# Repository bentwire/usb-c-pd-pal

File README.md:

# usb-c-pd-pal
100W USB C PD Power path with on board switches and current sensing.  Can take input from USB-C, Barell, or wire terminal, and output to wire terminal or USB-C.

This design can do up to 100W PD.  The switches and connectors are all rated for 5A, the max voltage is 21V so it can't do the extended power ranges.

There is a separate power path for both the 5V only and High Power paths.  The board is wired to be capable of both sink and source modes.

If you wish to make this board act as a source you will need to provide 5V to the 5V power path at the very least.

TODO:
Code forthcoming.
Still need to finish the layout.
Some parts won't be generally available until next year...

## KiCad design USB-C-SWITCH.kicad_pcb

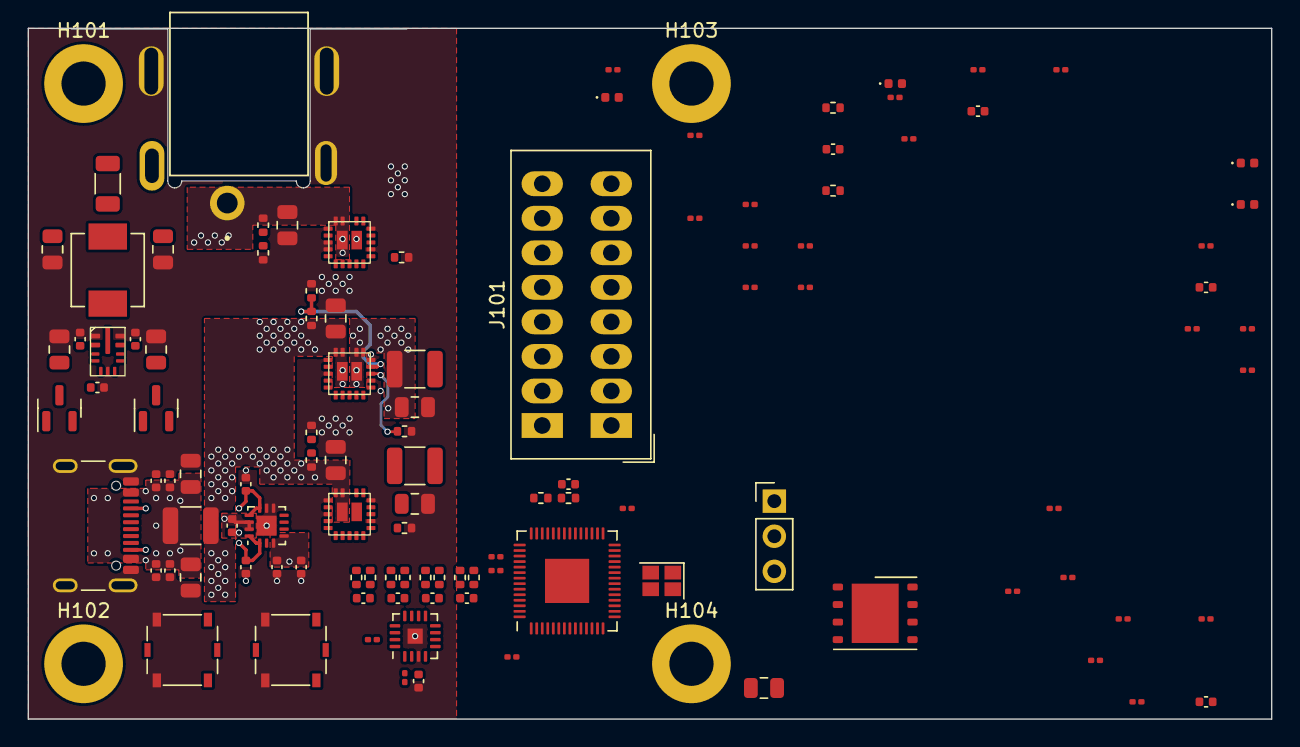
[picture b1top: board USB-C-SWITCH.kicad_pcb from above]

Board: 4 copper layers, 90.0 x 50.0 mm, 114 parts (0 on the bottom side), 70 nets.

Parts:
C201, C204, C301: 22UF 35V X5R; C_0805_2012Metric
C202, C205, C302: 10uF 35V; C_0805_2012Metric
C203, C206, C303, C404, C414: 100nF; C_0402_1005Metric
C401, C402, C406, C407, C408, C409, C419, C420: 0.1uF 50V X5R; C_0402_1005Metric
C403, C421: 1uF 10V X7S; C_0402_1005Metric
C405, C415: 0.1uF 10V X7R; C_0402_1005Metric
C410, C411, C417, C418: 4.7uF 50V X5R; C_0805_2012Metric
C412, C413: 330pF 50V; C_0402_1005Metric
C416: 11pF 50V; C_0402_1005Metric
C422, C423: 22uF 10V X5R; C_0805_2012Metric
C501, C502: 1uF 6.3V; C_0402_1005Metric
C503, C504, C505, C506, C507, C508, C509, C510, C511: 100nF 6.3V; C_0201_0603Metric
C512, C513: 27pF; C_0201_0603Metric
D401, D402: PMEG3005CT; SOT-23
D501, D502, D503, D504: TZ-P2-0402GTIA1-0.45T; LED_0402_1005Metric
H101, H102, H103, H104: MountingHole; MountingHole_3.2mm_M3_ISO7380_Pad
J101: Conn_01x08_Socket; TerminalBlock_Phoenix_PTSM-0,5-8-2.5-H-THR_1x08_P2.50mm_Hor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
J201: PJ-068B-SMT-TR; CUI_PJ-068B-SMT-TR
J401: USB_C_Receptacle_USB2.0; USB_C_Receptacle_GCT_USB4105-xx-A_16P_TopMnt_Horizontal
J501: Conn_01x03; PinHeader_1x03_P2.54mm_Vertical
L401: 6.8uH IHLP2020BZER6R8M01; L_Vishay_IHLP-2020
R201, R301, R401: 0.018R 1W 1%; R_1210_3225Metric
R202, R208: 165K 1%; R_0402_1005Metric
R203, R204, R303, R304, R402, R403, R406, R407: 10R; R_0402_1005Metric
R205, R210, R305: 10K 1%; R_0402_1005Metric
R206, R212, R307: 470R; R_0402_1005Metric
R207, R209, R306, R404, R405, R503, R504, R507: 10K; R_0201_0603Metric
R211: 5.62K 1%; R_0402_1005Metric
R213: 1K 1%; R_0402_1005Metric
R302: 34K 1%; R_0402_1005Metric
R408: 0.060R 1W 1%; R_1206_3216Metric
R409: 100K; R_0402_1005Metric
R410: 43.2K; R_0402_1005Metric
R501, R502: 4.7K; R_0201_0603Metric
R505, R506: 27R4; R_0201_0603Metric
R508, R509: 1K; R_0201_0603Metric
R510, R511, R512, R513: 470R; R_0201_0603Metric
SW501: RUN; SW_SPST_Panasonic_EVQPL_3PL_5PL_PT_A15
SW502: BOOT; SW_SPST_Panasonic_EVQPL_3PL_5PL_PT_A15
U201, U202, U301: UCS3205; 19-VQFN-Q8A-3x3x0.9-2EP
U401: FUSB302BMPX; WQFN-14-1EP_2.5x2.5mm_P0.5mm_EP1.45x1.45mm
U402: PAC1954x-x4MX; VQFN-16-1EP_3x3mm_P0.5mm_EP1.1x1.1mm
U403: LMR36006CRNX; TI-RNX0012A-VQFN-HR
U501: W25Q128JVPIQ; WSON-8-1EP_6x5mm_P1.27mm_EP3.4x4.3mm
U502: RP2040; QFN-56-1EP_7x7mm_P0.4mm_EP3.2x3.2mm
Y501: 12.000 MHz; Crystal_SMD_EuroQuartz_X22-4Pin_2.5x2.0mm

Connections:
+3.3VP: C401.1, C402.1, C403.1, C405.2, C501.2, C503.2, C504.2, C505.2, C506.2, C507.2, C508.2, C511.1, R207.1, R209.1, R306.1, R404.1, R405.1, R407.1, R408.2, R501.1, R502.1, R503.1, R504.1, R507.1, U401.3 (VDD), U401.4 (VDD), U401.12 (VCONN), U401.13 (VCONN), U402.2 (V_{DD}), U501.8 (VCC), U502.1 (IOVDD), U502.10 (IOVDD), U502.22 (IOVDD), U502.33 (IOVDD), U502.42 (IOVDD), U502.43 (ADC_AVDD), U502.44 (VREG_IN), U502.48 (USB_VDD), U502.49 (IOVDD)
/5V Power Path/5V-PP-VS+: C303.1, R303.2, U402.8 (SENSE3+)
/5V Power Path/5V-PP-VS-: C303.2, R304.2, U402.7 (SENSE3-)
/5V Power Path/VUSB_5V_DIR: U301.4 (DIR), U502.35 (GPIO23)
/5V Power Path/VUSB_5V_DSC: U301.5 (DSC), U502.36 (GPIO24)
/5V Power Path/VUSB_5V_EN: U301.2 (EN), U502.34 (GPIO22)
/5V Power Path/VUSB_5V_SENSE: C302.1, R301.1, R303.1, U301.16 (VOUT), U301.17 (VOUT), U301.VOUT
/5V Power Path/VUSB_5V_~FAULT: R306.2, U301.11 (~FAULT), U502.37 (GPIO25)
/PD Current Sense and USB-C/D+: J401.A6 (D+), J401.B6 (D+), R505.1
/PD Current Sense and USB-C/D-: J401.A7 (D-), J401.B7 (D-), R506.1
/PD Current Sense and USB-C/PD-SENSE-~ALERT1: R404.2, U402.1 (SLOW), U502.5 (GPIO3)
/PD Current Sense and USB-C/PD-SENSE-~ALERT2: R405.2, U402.15 (GPIO), U502.6 (GPIO4)
/PD Current Sense and USB-C/PD-SENSE-~PWRDN: U402.16 (~PWRDN), U502.7 (GPIO5)
/PD Current Sense and USB-C/PP-VS+: C203.1, R203.2, U402.13 (SENSE2+)
/PD Current Sense and USB-C/PP-VS-: C203.2, R204.2, U402.14 (SENSE2-)
/PD Current Sense and USB-C/SCL: R502.2, U401.6 (SCL), U402.4 (SCL), U502.3 (GPIO1)
/PD Current Sense and USB-C/SDA: R501.2, U401.7 (SDA), U402.5 (SDA), U502.2 (GPIO0)
/PD Current Sense and USB-C/USB-C-~INT: R503.2, U401.5 (INT_N), U502.4 (GPIO2)
/PD Current Sense and USB-C/VBUS_SENSE: C406.1, C407.1, C408.1, C409.1, C410.1, C411.1, J401.A4 (VBUS), J401.A9 (VBUS), J401.B4 (VBUS), J401.B9 (VBUS), R401.1, R402.1, U401.2 (VBUS)
/PD Power Path/ADAP-EN: U202.2 (EN), U502.31 (GPIO20)
/PD Power Path/ADAP-VSNS: C206.2, R211.2, R213.1, U502.38 (GPIO26_ADC0)
/PD Power Path/ADAP-~FAULT: R209.2, U202.11 (~FAULT), U502.32 (GPIO21)
/PD Power Path/ADAPTER_VIN: C204.1, D402.2 (A), J201.1, R208.1, R211.1, U202.19 (VIN), U202.20 (VIN), U202.VIN
/PD Power Path/PP-DIR: U201.4 (DIR), U502.28 (GPIO17)
/PD Power Path/PP-DSC: U201.5 (DSC), U202.5 (DSC), U502.29 (GPIO18)
/PD Power Path/PP-EN: U201.2 (EN), U502.27 (GPIO16)
/PD Power Path/PP-~FAULT: R207.2, U201.11 (~FAULT), U502.30 (GPIO19)
/PP-5V: D401.2 (A), R301.2, R304.1
/PP-HV: D402.1 (A), R201.2, R204.1
/RP2040/RUN: R504.2, SW501.2, U502.26 (RUN)
/VBUS: C201.1, C301.1, D401.1 (A), R202.1, R302.1, R401.2, R403.1, U201.19 (VIN), U201.20 (VIN), U201.VIN, U301.19 (VIN), U301.20 (VIN), U301.VIN
GND: C201.2, C202.2, C204.2, C205.2, C206.1, C301.2, C302.2, C401.2, C402.2, C403.2, C405.1, C406.2, C407.2, C408.2, C409.2, C410.2, C411.2, C412.1, C413.1, C417.2, C418.2, C419.2, C420.2, C421.2, C422.1, C423.1, C501.1, C502.1, C503.1, C504.1, C505.1, C506.1, C507.1, C508.1, C509.1, C510.1, C511.2, C512.2, C513.2, D501.1 (K), D502.1 (K), D503.1 (K), D504.1 (K), J201.2, J201.4 (SHIELD), J201.5 (SHIELD__1), J401.A1 (GND), J401.A12 (GND), J401.B1 (GND), J401.B12 (GND), J401.S1 (SHIELD), J501.2, R205.2, R206.2, R210.2, R212.2, R213.2, R305.2, R307.2, R410.2, SW501.1, SW502.1, U201.1 (GND), U201.3 (FRS), U201.12 (LATCH), U201.15 (GND), U202.1 (GND), U202.3 (FRS), U202.4 (DIR), U202.12 (LATCH), U202.15 (GND), U301.1 (GND), U301.3 (FRS), U301.12 (LATCH), U301.15 (GND), U401.8 (GND), U401.9 (GND), U401.15 (GND), U402.3 (GND), U402.17 (EP), U403.1 (PGND), U403.6 (AGND), U403.11 (PGND), U501.4 (GND), U502.57 (GND), Y501.2, Y501.4
unnamed: C202.1, C205.1, R201.1, R203.1, U201.16 (VOUT), U201.17 (VOUT), U201.VOUT, U202.16 (VOUT), U202.17 (VOUT), U202.VOUT
unnamed: C416.2, C422.2, C423.2, L401.2, R406.1, R408.1, R409.1
unnamed: C512.1, R509.1, Y501.1
unnamed: C417.1, C418.1, C419.1, C420.1, D401.3 (K), D402.3 (K), U403.2 (VIN), U403.9 (EN), U403.10 (VIN)
unnamed: D501.2 (A), R510.2
unnamed: D502.2 (A), R511.2
unnamed: D503.2 (A), R512.2
unnamed: D504.2 (A), R513.2
unnamed: C413.2, J401.A5 (CC1), U401.10 (CC1), U401.11 (CC1)
unnamed: C412.2, J401.B5 (CC2), U401.1 (CC2), U401.14 (CC2)
unnamed: J501.1, U502.24 (SWCLK)
unnamed: J501.3, U502.25 (SWD)
unnamed: R508.1, SW502.2
unnamed: R206.1, U201.13 (ISEN)
unnamed: R202.2, R205.1, U201.14 (VOV)
unnamed: R212.1, U202.13 (ISEN)
unnamed: R208.2, R210.1, U202.14 (VOV)
unnamed: R307.1, U301.13 (ISEN)
unnamed: R302.2, R305.1, U301.14 (VOV)
unnamed: C404.1, R402.2, U402.11 (SENSE1+)
unnamed: C404.2, R403.2, U402.12 (SENSE1-)
unnamed: C414.1, R406.2, U402.10 (SENSE4+)
unnamed: C414.2, R407.2, U402.9 (SENSE4-)
unnamed: C415.1, U403.4 (BOOT)
unnamed: C416.1, R409.2, R410.1, U403.7 (FB)
unnamed: C415.2, L401.1, U403.3 (NC/SW), U403.12 (SW)
unnamed: C421.1, U403.5 (VCC)
unnamed: U501.6 (CLK), U502.52 (QSPI_SCLK)
unnamed: U501.5 (DI(IO0)), U502.53 (QSPI_SD0)
unnamed: U501.2 (DO(IO1)), U502.55 (QSPI_SD1)
unnamed: U501.3 (IO2), U502.54 (QSPI_SD2)
unnamed: U501.7 (IO3), U502.51 (QSPI_SD3)
unnamed: R507.2, R508.2, U501.1 (~CS), U502.56 (QSPI_SS)
unnamed: R506.2, U502.46 (USB_DM)
unnamed: R505.2, U502.47 (USB_DP)
unnamed: C502.2, C509.2, C510.2, U502.23 (DVDD), U502.45 (VREG_VOUT), U502.50 (DVDD)
unnamed: C513.1, U502.20 (XIN), Y501.3
unnamed: R509.2, U502.21 (XOUT)

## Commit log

2023-11-09 Initial import, Schematic 99% done, Some routing and placement done.
2023-11-09 Add pdf/svg of schematic.
